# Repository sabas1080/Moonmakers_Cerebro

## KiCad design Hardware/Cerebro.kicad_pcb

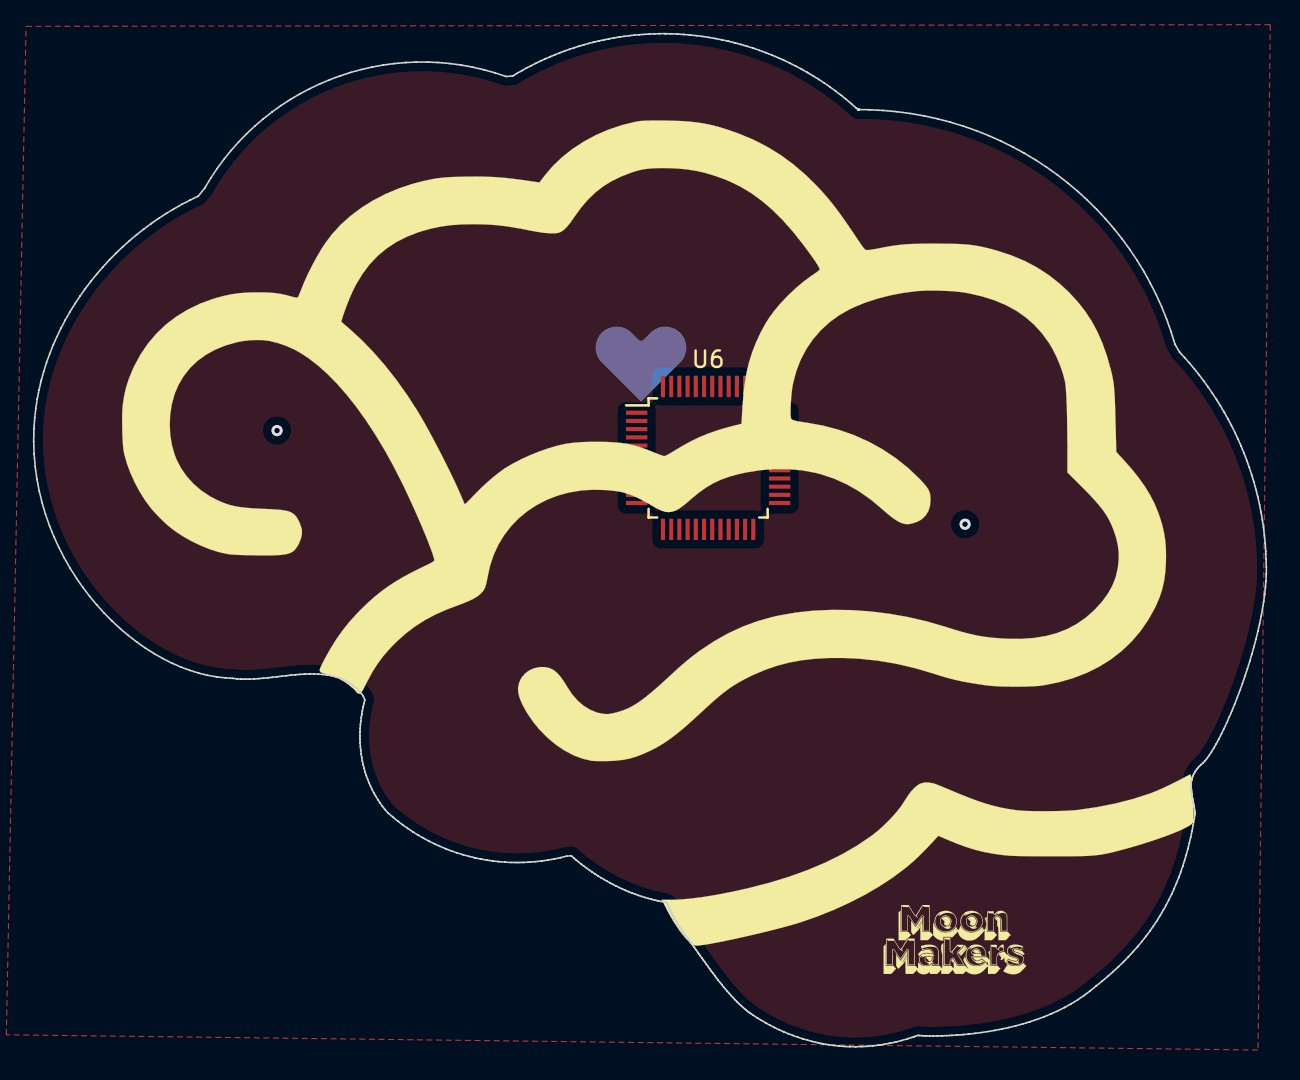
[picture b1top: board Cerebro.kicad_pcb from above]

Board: 2 copper layers, 75.0 x 61.7 mm, 3 parts (1 on the bottom side), 2 nets, no tracks yet.

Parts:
Ref**: Val**; Cerebro_001
U6: ATSAMD21G18A-AUT; TQFP-48_7x7mm_P0.5mm
svg2mod: G***; heart

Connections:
unnamed: U6.17, U6.36
unnamed: U6.18, U6.35, U6.42

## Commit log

2019-10-25 initial commits
2019-10-25 update samd21e
2019-10-25 add logo
2019-10-25 add gitignore
2019-10-25 update pcb
2019-10-28 basic componets
2019-10-28 schematic
